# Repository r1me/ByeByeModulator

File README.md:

# ByeByeModulator
Modulator replacement for Commodore 64. The idea of this small board is to improve picture quality by removing noise that is caused by an RF modulator and its old electronic components. Including capacitors that can't be accessed easily for replacement, without desoldering a modulator first.  
This board is designed for, and tested with **250469 rev. B motherboard**. Do **NOT** even attempt to install it in other motherboards i.e. the one with 656x VIC-II chip. I'm not responsible for any damage.

## Board
It is a single sided, DIY friendly board.  
[Schematic](ByeByeModulator-schematic.pdf)  
[Back side for print](ByeByeModulator-board.png)  

## Results
Before & after

What I personally like about result is: rich colors (mostly yellow and green), not over-bright, and much cleaner text in the BASIC. There is some weird "wave" pattern going on, that I tried to fix by shortening L2 on C64 motherboard, it helped a bit.

## Space for improvement (aka work in progress)
If you have any idea how to improve this board, but at the same time keep it as simple as possible - feel free to fork this repository.

Thanks to aniol @ [c64scene.pl](http://www.c64scene.pl).

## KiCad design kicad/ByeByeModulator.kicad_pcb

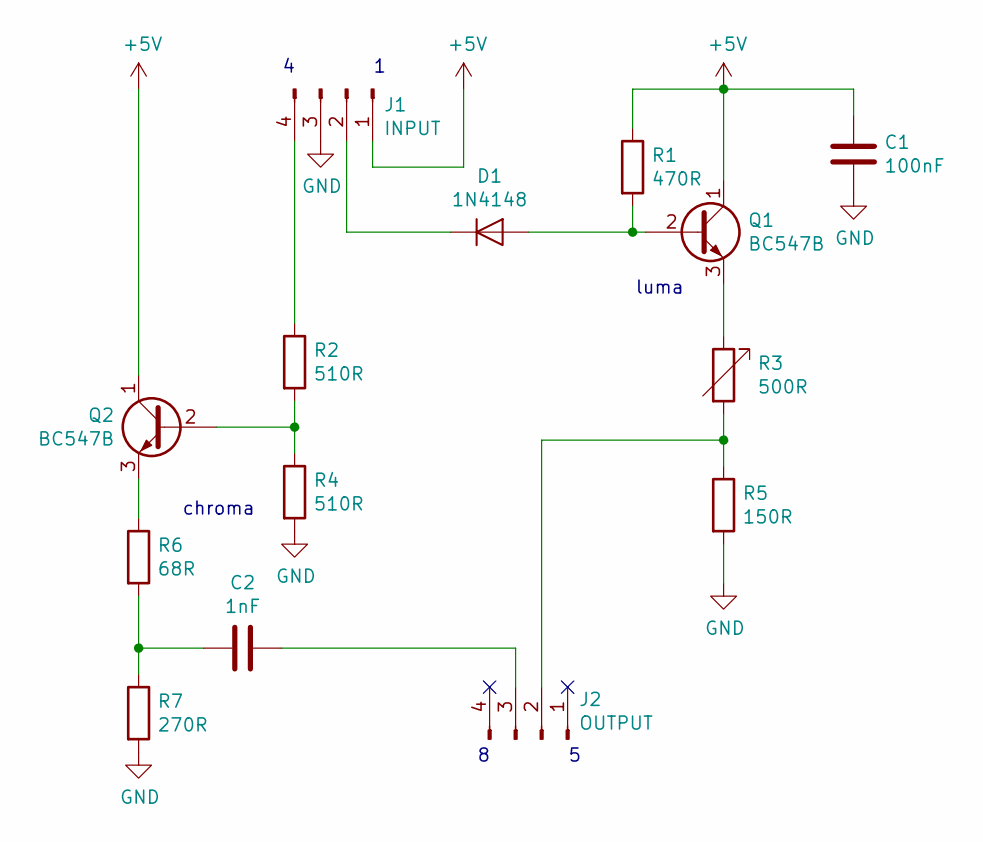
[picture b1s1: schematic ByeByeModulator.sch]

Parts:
C1: 100nF; C_Rect_L7.0mm_W2.5mm_P5.00mm
C2: 1nF; C_Disc_D5.0mm_W2.5mm_P5.00mm
D1: 1N4148; D_DO-35_SOD27_P7.62mm_Horizontal
J1: INPUT; Pin_Header_Straight_1x04_Pitch2.54mm
J2: OUTPUT; Pin_Header_Straight_1x04_Pitch2.54mm
Q1, Q2: BC547B; TO-92_Inline_Wide
R1: 470R; R_Axial_DIN0207_L6.3mm_D2.5mm_P10.16mm_Horizontal
R2, R4: 510R; R_Axial_DIN0207_L6.3mm_D2.5mm_P10.16mm_Horizontal
R3: 500R; Potentiometer_Trimmer_Bourns_3296W
R5: 150R; R_Axial_DIN0207_L6.3mm_D2.5mm_P10.16mm_Horizontal
R6: 68R; R_Axial_DIN0207_L6.3mm_D2.5mm_P10.16mm_Horizontal
R7: 270R; R_Axial_DIN0207_L6.3mm_D2.5mm_P10.16mm_Horizontal

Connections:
+5V: C1.1, J1.1, Q1.1 (C), Q2.1 (C), R1.1
GND: C1.2, J1.3, R4.2, R5.2, R7.2
unnamed: C2.1, J2.3
unnamed: C2.2, R6.2, R7.1
unnamed: D1.1 (K), J1.2
unnamed: D1.2 (A), Q1.2 (B), R1.2
unnamed: J1.4, R2.1
unnamed: J2.2, R3.2, R5.1
unnamed: Q1.3 (E), R3.1
unnamed: Q2.2 (B), R2.2, R4.1
unnamed: Q2.3 (E), R6.1

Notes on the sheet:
chroma
luma

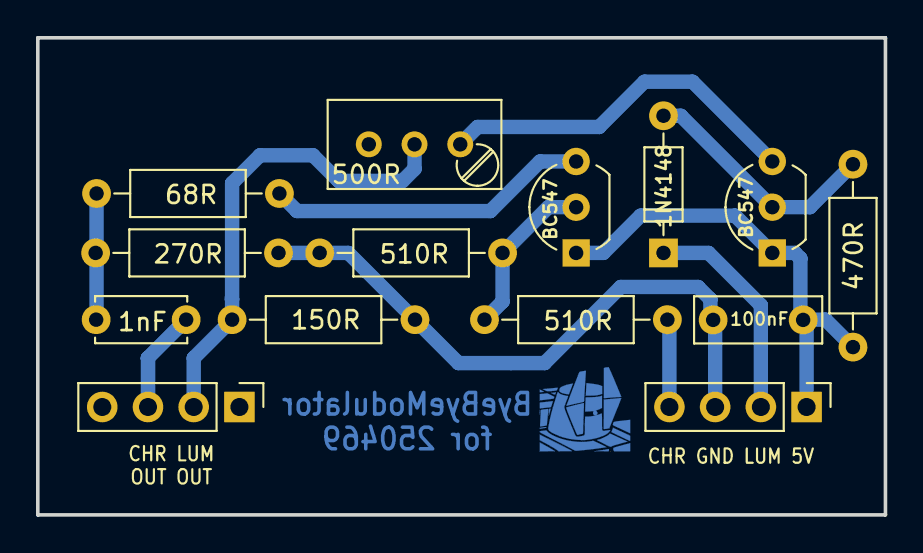
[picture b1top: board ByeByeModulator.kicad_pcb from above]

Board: 2 copper layers, 47.1 x 26.5 mm, 14 parts (0 on the bottom side), 11 nets.

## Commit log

2019-02-12 3D preview
2019-02-12 Cheap video grabber screenshots of my results
2019-02-12 Photo of installed ByeByeModulator
2019-02-12 Added readme
2019-02-12 Shorted L2
